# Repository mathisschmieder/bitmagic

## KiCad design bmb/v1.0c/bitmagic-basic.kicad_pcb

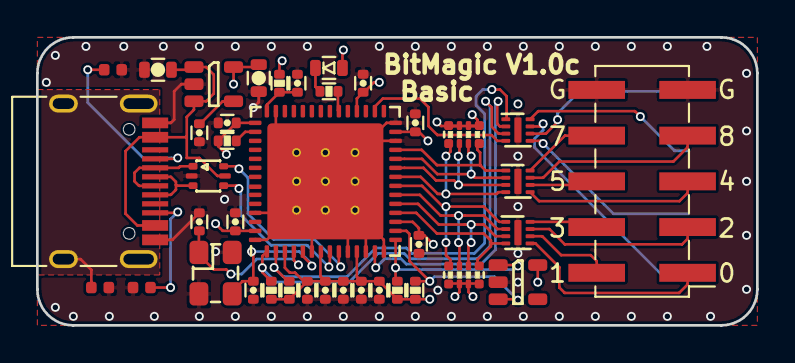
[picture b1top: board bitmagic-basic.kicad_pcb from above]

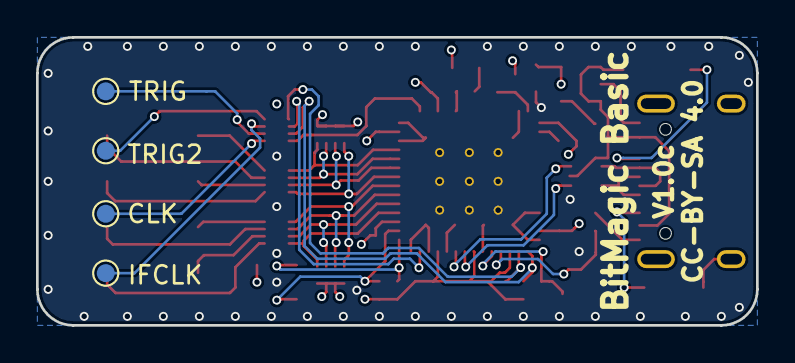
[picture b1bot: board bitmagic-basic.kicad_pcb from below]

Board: 4 copper layers, 40.0 x 16.0 mm, 43 parts (4 on the bottom side), 43 nets.

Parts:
C1, C2, C3, C4, C5, C6, C9, C10: 100n; C_0402
C7, C8: 2u2; C_0402
C11, C13: 4u7; C_0603
C12: 10n; C_0402
C14: 1u; C_0402
C15, C16: 10p; C_0402
D1: GRN; D_0603
IC1: CY7C68013A-56; QFN-56-1EP_8x8mm_Pitch0.5mm
J1: Conn_02x05_Odd_Even; PinHeader_2x05_P2.54mm_Vertical_SMD
J2: Host_USB_C; USB_C_Receptacle_HRO_TYPE-C-31-M-12
R1: 330E; R_0402
R2, R3, R4: 2k7; R_0402
R5, R6, R7: 100k; R_0402
R8, R9: 150k; R_Array_Convex_4x0402
R10: 1m; R_0402_1005Metric
R11, R12: 5k1; R_0402_1005Metric
TP1: T1; TestPoint_Pad_D1.0mm
TP2: T2; TestPoint_Pad_D1.0mm
TP3: CLK; TestPoint_Pad_D1.0mm
TP4: IFCLK; TestPoint_Pad_D1.0mm
U1: 3.3V; SOT-23-5
U2: USBLC6-2; SOT-666
U3, U4, U6: IP425x-4-TTL; DFN-8-1EP_1.35x1.7mm_Pitch0.4mm
U5: 24LC00; SOT-23-5
X1: 24MHz; ABM8

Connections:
+3V3: C1.1, C2.1, C3.1, C4.1, C5.1, C6.1, C7.1, C8.1, C9.1, C10.1, C13.1, D1.A, IC1.3, IC1.7, IC1.11, IC1.17, IC1.27, IC1.32, IC1.43, IC1.55, R2.2, R3.2, R4.2, R5.2, R6.1, R7.1, R8.2, R8.4, R8.6, R8.8, R9.2, R9.4, R9.6, R9.8, U1.5, U5.5
+5V: C11.1, J2.A4, J2.A9, J2.B4, J2.B9, U1.1, U1.3, U2.5
/CLK: IC1.30, U6.4
/IFCLK: IC1.13, U6.2
/PA1: IC1.34, R1.2
/PB0: IC1.18, R8.1, U3.4
/PB1: IC1.19, R8.3, U3.3
/PB2: IC1.20, R8.5, U3.2
/PB3: IC1.21, R8.7, U3.1
/PB4: IC1.22, R9.1, U4.4
/PB5: IC1.23, R9.3, U4.3
/PB6: IC1.24, R9.5, U4.2
/PB7: IC1.25, R9.7, U4.1
/SCL: IC1.15, R2.1, U5.1
/SDA: IC1.16, R3.1, U5.3
/TRIG: IC1.1, R6.2, U6.3
/TRIG2: IC1.2, R7.2, U6.1
/USBD_N: IC1.9, U2.6
/USBD_P: IC1.8, U2.4
/WAKEUP: IC1.44, R5.1
/XTALIN: C16.1, IC1.5, X1.2
/XTALOUT: C15.1, IC1.4, X1.1
/shield: J2.S1, R10.2
/xCLK: TP3.1, U6.5
/xIFCLK: TP4.1, U6.7
/xPB0: J1.1, U3.5
/xPB1: J1.2, U3.6
/xPB2: J1.3, U3.7
/xPB3: J1.4, U3.8
/xPB4: J1.5, U4.5
/xPB5: J1.6, U4.6
/xPB6: J1.7, U4.7
/xPB7: J1.8, U4.8
/xTRIG: TP1.1, U6.6
/xTRIG2: TP2.1, U6.8
/xUSBD_N: J2.A7, J2.B7, U2.1
/xUSBD_P: J2.A6, J2.B6, U2.3
/~RESET: C14.1, IC1.42, R4.1
GND: C1.2, C2.2, C3.2, C4.2, C5.2, C6.2, C7.2, C8.2, C9.2, C10.2, C11.2, C12.2, C13.2, C14.2, C15.2, C16.2, IC1.6, IC1.10, IC1.12, IC1.14, IC1.26, IC1.28, IC1.41, IC1.53, IC1.56, IC1.57, J1.9, J1.10, J2.A1, J2.A12, J2.B1, J2.B12, R10.1, R11.1, R12.1, U1.2, U2.2, U3.9, U4.9, U5.2, U6.9, X1.GND
unnamed: C12.1, U1.4
unnamed: D1.C, R1.1
unnamed: J2.A5, R11.2
unnamed: J2.B5, R12.2

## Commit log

2020-05-17 Initial commit of v1.0c
    Added USB Type C connector
    Added 0.1" pitch frontend connector
2020-05-20 Renamed v1.0c to Type-C
2020-06-08 Factory 0402 footprint to pkl 0402, silkscreen fixes
    The USB Type C 5k1 resistors used factory KiCAD footprints and are now pkl as all the others.
    Pin 6 is now correctly marked

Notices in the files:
bmb/v1.0c/bitmagic-basic.kicad_pcb:
CC-BY-SA V4.0
(C) 2019 1BitSquared
(C) 2019 Piotr Esden-Tempski
CC-BY-SA 4.0
